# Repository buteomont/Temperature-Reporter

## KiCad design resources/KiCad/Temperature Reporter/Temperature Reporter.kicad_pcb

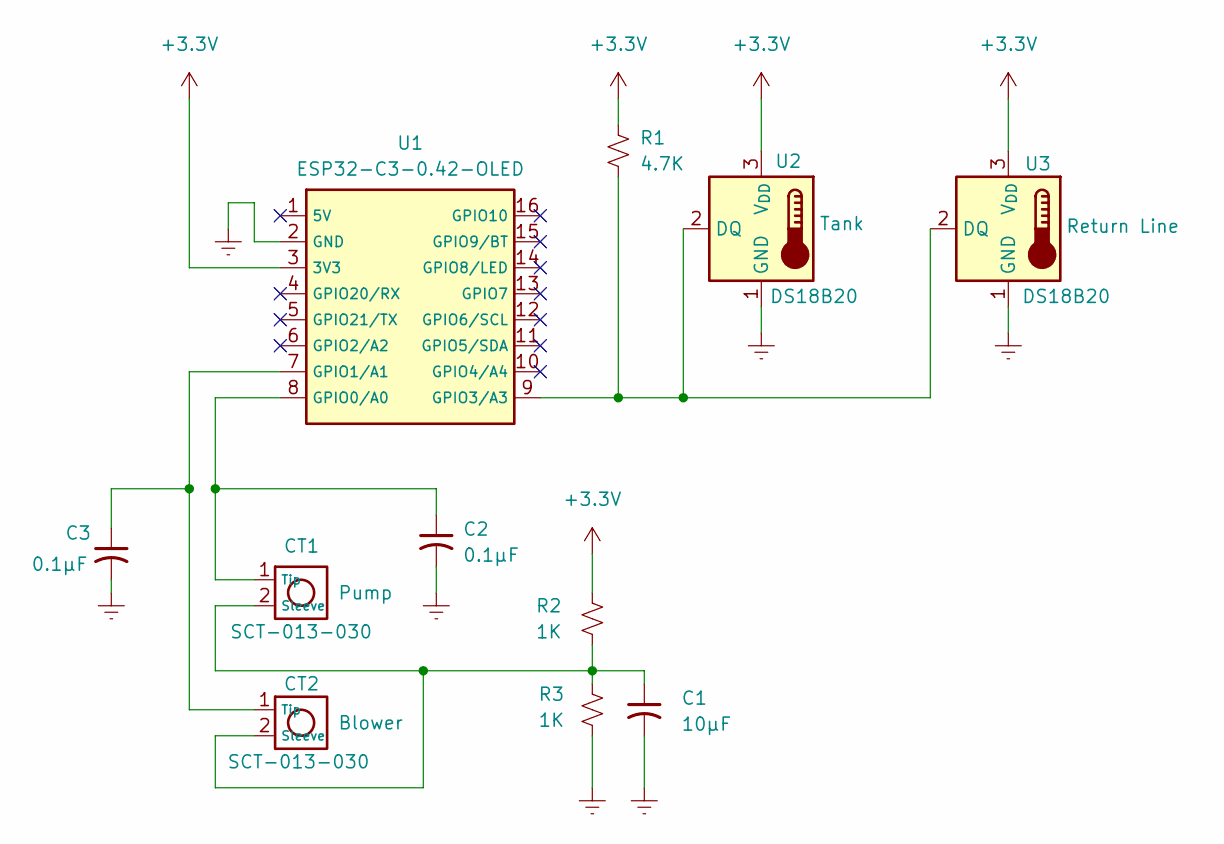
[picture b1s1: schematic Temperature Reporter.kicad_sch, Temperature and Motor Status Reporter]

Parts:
C1: 10μF; C_Disc_D3.4mm_W2.1mm_P2.50mm
C2, C3: 0.1μF; C_Disc_D3.4mm_W2.1mm_P2.50mm
CT1: Pump; PinHeader_1x02_P2.54mm_Horizontal
CT2: Blower; PinHeader_1x02_P2.54mm_Horizontal
R1: 4.7K; R_Axial_DIN0204_L3.6mm_D1.6mm_P2.54mm_Vertical
R2, R3: 1K; R_Axial_DIN0204_L3.6mm_D1.6mm_P2.54mm_Vertical
U1: ESP32-C3-0.42-OLED; ESP32-C3-OLED
U2, U3: DS18B20; PinHeader_1x03_P2.54mm_Horizontal

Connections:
+3.3V: R1.1, R2.1, U1.3 (3V3), U2.3 (V_{DD}), U3.3 (V_{DD})
Earth: C1.2, C2.2, C3.2, R3.2, U1.2 (GND), U2.1 (GND), U3.1 (GND)
unnamed: C1.1, CT1.2 (Sleeve), CT2.2 (Sleeve), R2.2, R3.1
unnamed: C2.1, CT1.1 (Tip), U1.8 (GPIO0/A0)
unnamed: C3.1, CT2.1 (Tip), U1.7 (GPIO1/A1)
unnamed: R1.2, U1.9 (GPIO3/A3), U2.2 (DQ), U3.2 (DQ)

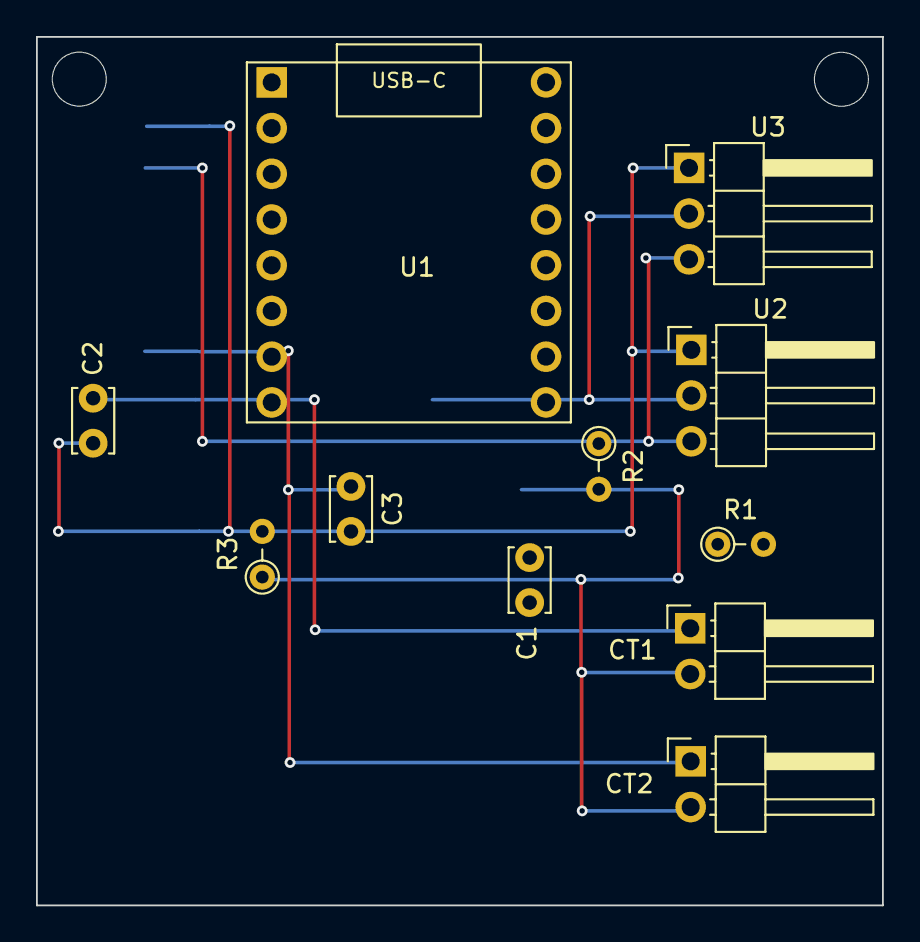
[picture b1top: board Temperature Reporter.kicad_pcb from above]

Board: 2 copper layers, 47.0 x 48.2 mm, 11 parts (0 on the bottom side), 6 nets.

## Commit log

2025-12-14 Initial commit.
2025-12-14 Adjusted ignore file
2025-12-14 Convert commands to lowercase before compare
2025-12-14 Added code to flip the display colors every 30 minutes for burn-in protection
2025-12-15 Fixed JSOn error. Reduced attenuation for current sensors. Blue LED for wifi.
2025-12-15 Set the attenuation back to 11db
2025-12-15 Added filter capacitors to the analog inputs
2025-12-15 updated schematic
2025-12-23 Changes to circuit board, board mount. Added code to set the power to maximum.
